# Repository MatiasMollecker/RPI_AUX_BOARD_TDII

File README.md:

# RPI_AUX_BOARD_TDII

## Description:
This is an auxiliary board designed to be mounted on Raspberry Pi models 3, 3 B+, 4 B, and 5. It includes LEDs, buttons, and a DIP switch to facilitate GPIO management.

For ADC functionality, I recommend using the ADS1115.

This board is particularly useful for carrying out practical work related to the subject *Técnicas Digitales II* (TDII) in 2024.

## Images:
### Down View (3D Model)

### Lateral View (3D Model)

### PCB Design

### Schematic Design

### Up View (3D Model)

## Credits:
Developed by Matías Mollecker.

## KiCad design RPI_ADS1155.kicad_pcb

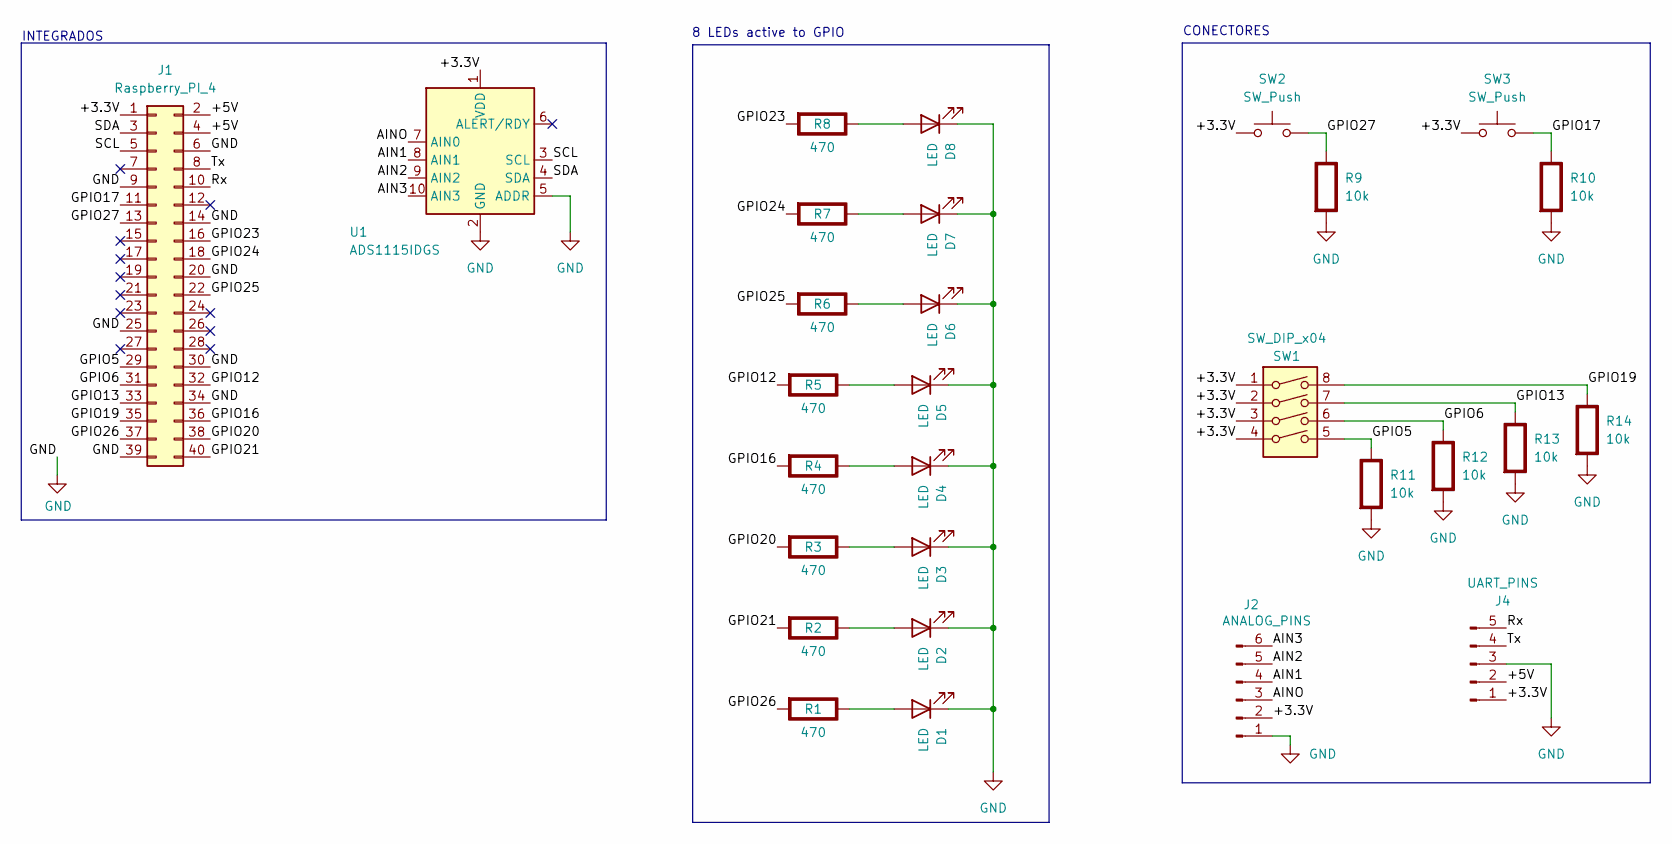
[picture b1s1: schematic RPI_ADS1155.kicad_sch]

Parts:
D1, D2, D3, D4, D5, D6, D7, D8: LED; LED_D5.0mm
J1: Raspberry_PI_4; PinSocket_2x20_P2.54mm_Vertical_SMD
J2: ANALOG_PINS; PinSocket_1x06_P2.54mm_Vertical
J4: UART_PINS; PinSocket_1x05_P2.54mm_Vertical
R1, R2, R3, R4, R5, R6, R7, R8: 470; R_Axial_DIN0207_L6.3mm_D2.5mm_P7.62mm_Horizontal; Rating W
R9, R10, R11, R12, R13, R14: 10k; R_Axial_DIN0207_L6.3mm_D2.5mm_P7.62mm_Horizontal; Rating W
SW1: SW_DIP_x04; SW_DIP_SPSTx04_Slide_6.7x11.72mm_W7.62mm_P2.54mm_LowProfile
SW2, SW3: SW_Push; SW_PUSH_6mm_H9.5mm
U1: ADS1115IDGS; Adafruit_ADS1115_modular

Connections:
/+3.3V: J1.1, J2.2, J4.1, SW1.1, SW1.2, SW1.3, SW1.4, SW2.1, SW3.1, U1.1 (VDD)
/+5V: J1.2, J1.4, J4.2
/AIN1: J2.4, U1.8 (AIN1)
/AIN2: J2.5, U1.9 (AIN2)
/AIN3: J2.6, U1.10 (AIN3)
/AINO: J2.3, U1.7 (AIN0)
/GPIO5: J1.29, R11.1 (+), SW1.5
/GPIO6: J1.31, R12.1 (+), SW1.6
/GPIO12: J1.32, R5.2 (-)
/GPIO13: J1.33, R13.1 (+), SW1.7
/GPIO16: J1.36, R4.2 (-)
/GPIO17: J1.11, R10.1 (+), SW3.2
/GPIO19: J1.35, R14.1 (+), SW1.8
/GPIO20: J1.38, R3.2 (-)
/GPIO21: J1.40, R2.2 (-)
/GPIO23: J1.16, R8.2 (-)
/GPIO24: J1.18, R7.2 (-)
/GPIO25: J1.22, R6.2 (-)
/GPIO26: J1.37, R1.2 (-)
/GPIO27: J1.13, R9.1 (+), SW2.2
/Rx: J1.10, J4.5
/SCL: J1.5, U1.3 (SCL)
/SDA: J1.3, U1.4 (SDA)
/Tx: J1.8, J4.4
GND: D1.1 (K), D2.1 (K), D3.1 (K), D4.1 (K), D5.1 (K), D6.1 (K), D7.1 (K), D8.1 (K), J1.6, J1.9, J1.14, J1.20, J1.25, J1.30, J1.34, J1.39, J2.1, J4.3, R9.2 (-), R10.2 (-), R11.2 (-), R12.2 (-), R13.2 (-), R14.2 (-), U1.2 (GND), U1.5 (ADDR)
unnamed: D1.2 (A), R1.1 (+)
unnamed: D2.2 (A), R2.1 (+)
unnamed: D3.2 (A), R3.1 (+)
unnamed: D4.2 (A), R4.1 (+)
unnamed: D5.2 (A), R5.1 (+)
unnamed: D6.2 (A), R6.1 (+)
unnamed: D7.2 (A), R7.1 (+)
unnamed: D8.2 (A), R8.1 (+)

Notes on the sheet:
8 LEDs active to GPIO
CONECTORES
INTEGRADOS

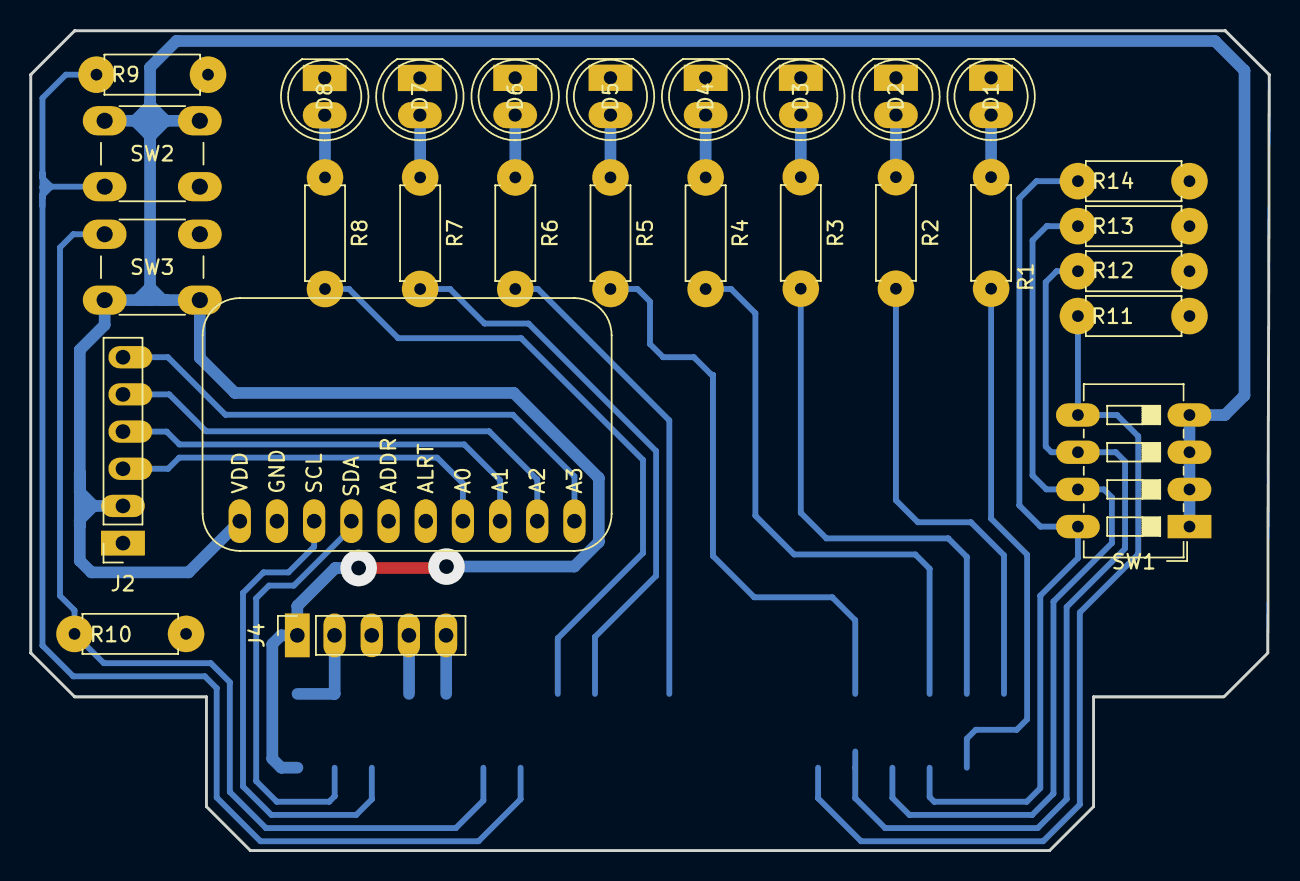
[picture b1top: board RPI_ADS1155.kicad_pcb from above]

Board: 2 copper layers, 84.6 x 56.0 mm, 29 parts (1 on the bottom side), 33 nets.

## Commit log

2024-09-22 Add kicad files
2024-09-22 Add images directory
2024-09-22 Add complete boards anda images
2024-10-02 Add UART connector and pins
2024-10-02 Add readme photos
2024-10-02 Expand vias holes for easy manual soldering
2024-10-02 Rm REEADME.html file
